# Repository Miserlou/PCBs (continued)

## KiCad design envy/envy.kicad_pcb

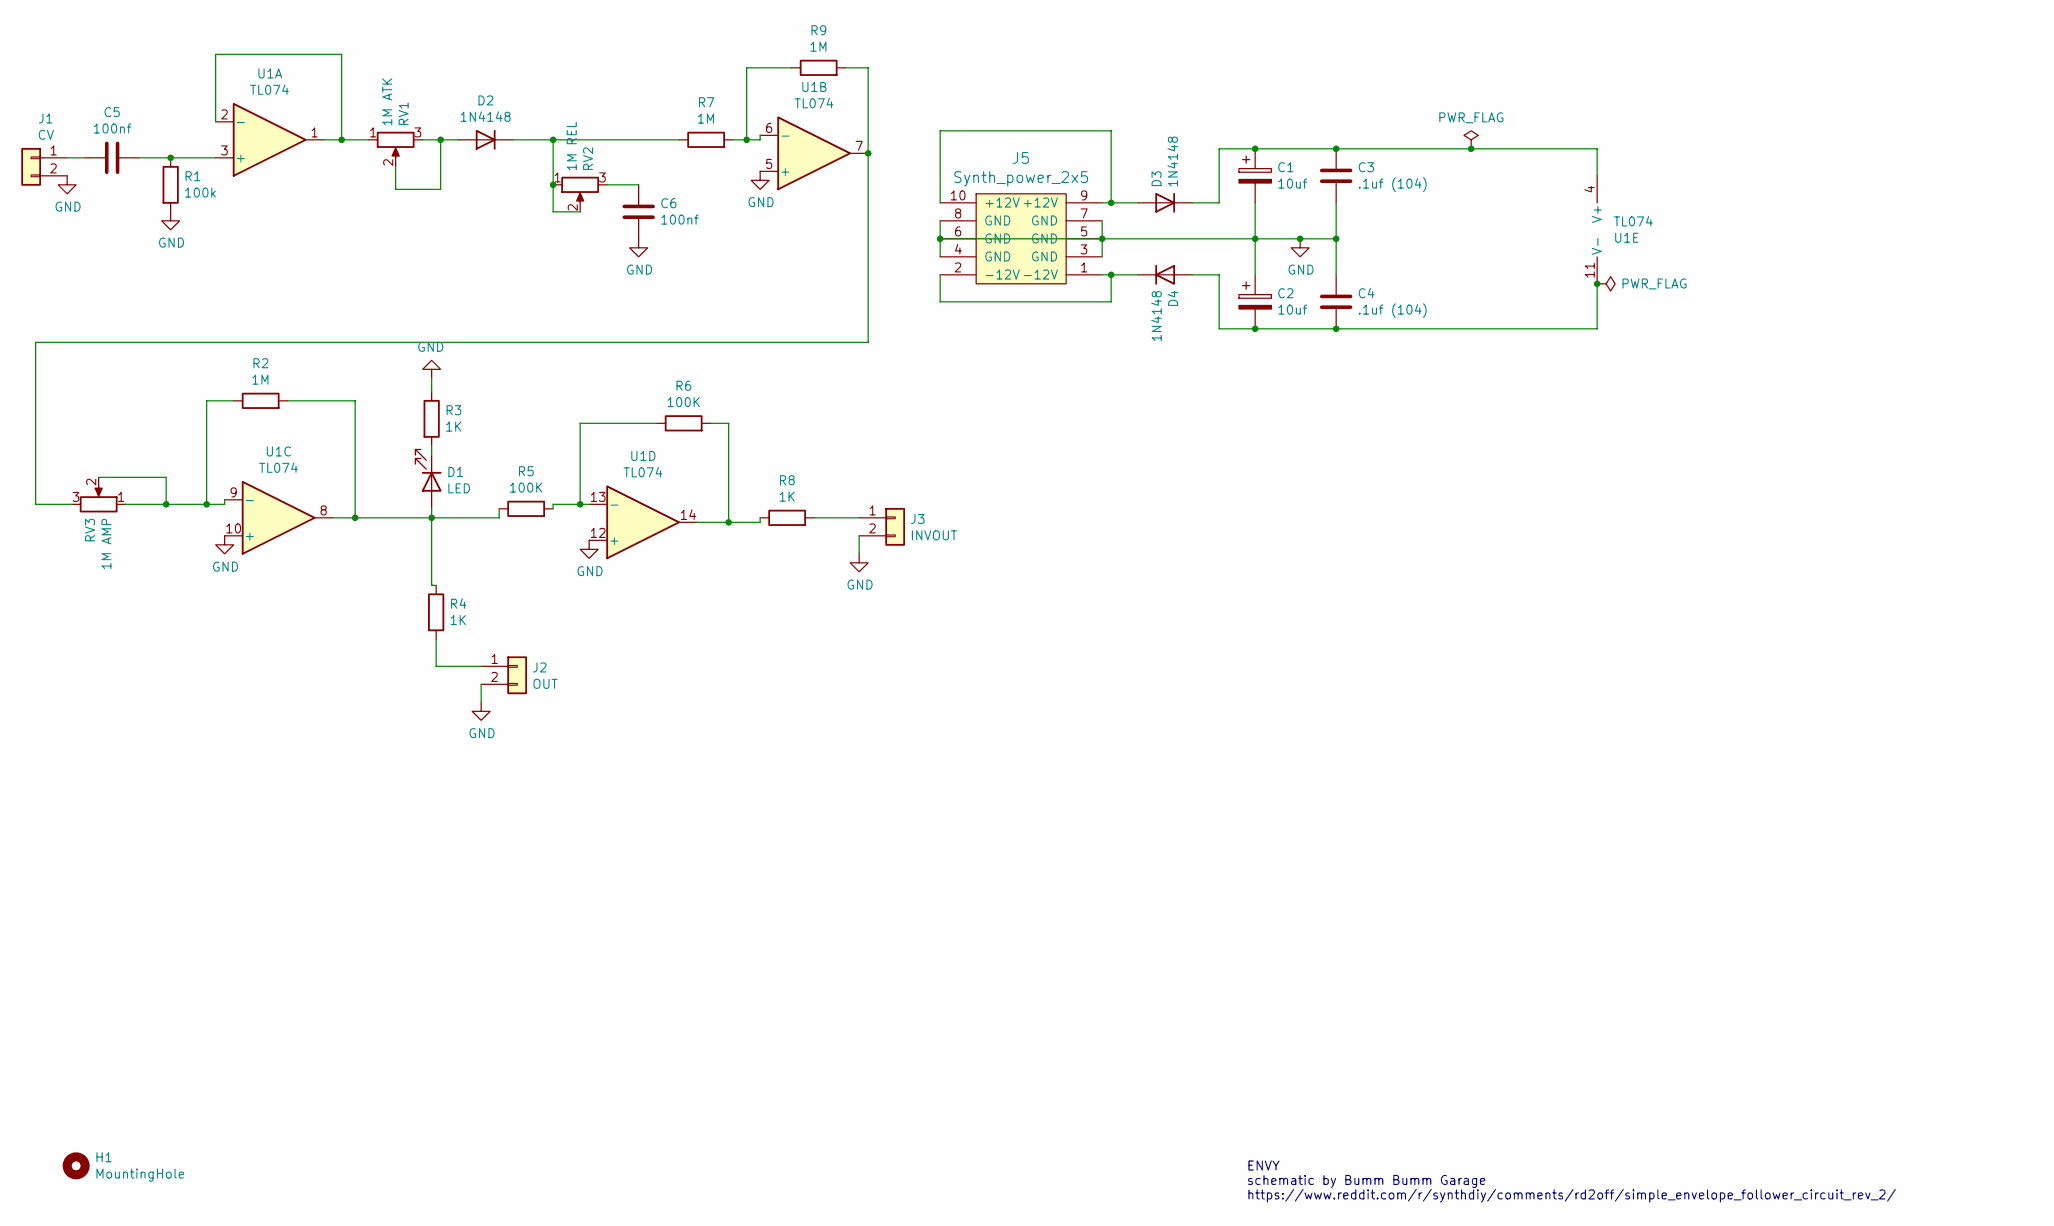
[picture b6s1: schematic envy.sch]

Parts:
C1, C2: 10uf; CP_Radial_D5.0mm_P2.00mm
C3, C4: .1uf (104); C_Disc_D3.0mm_W1.6mm_P2.50mm
C5, C6: 100nf; C_Disc_D3.0mm_W1.6mm_P2.50mm
D1: LED; LED_D5.0mm
D2, D3, D4: 1N4148; D_DO-35_SOD27_P7.62mm_Horizontal
H1: MountingHole; MountingHole_3.2mm_M3
J1: CV; Molex_KK-254_AE-6410-02A_1x02_P2.54mm_Vertical
J2: OUT; Molex_KK-254_AE-6410-02A_1x02_P2.54mm_Vertical
J3: INVOUT; Molex_KK-254_AE-6410-02A_1x02_P2.54mm_Vertical
J5: Synth_power_2x5; Power_Header
R1: 100k; R_Axial_DIN0207_L6.3mm_D2.5mm_P7.62mm_Horizontal
R2, R7, R9: 1M; R_Axial_DIN0207_L6.3mm_D2.5mm_P7.62mm_Horizontal
R3, R4, R8: 1K; R_Axial_DIN0207_L6.3mm_D2.5mm_P7.62mm_Horizontal
R5, R6: 100K; R_Axial_DIN0207_L6.3mm_D2.5mm_P7.62mm_Horizontal
RV1: 1M ATK; Potentiometer_Alpha_RD901F-40-00D_Single_Vertical_CircularH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
RV2: 1M REL; Potentiometer_Alpha_RD901F-40-00D_Single_Vertical_CircularH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
RV3: 1M AMP; Potentiometer_Alpha_RD901F-40-00D_Single_Vertical_CircularH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
U1: TL074; DIP-14_W7.62mm_Socket_LongPads

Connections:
GND: C1.2, C2.1, C3.2, C4.1, C6.2, J1.2, J2.2, J3.2, J5.3 (GND), J5.4 (GND), J5.5 (GND), J5.6 (GND), J5.7 (GND), J5.8 (GND), R1.2, R3.1, U1.5 (+), U1.10 (+), U1.12 (+); also elsewhere on the board
unnamed: C1.1, C3.1, D3.1 (K), U1.4 (V+)
unnamed: C2.2, C4.2, D4.2 (A), U1.11 (V-)
unnamed: C5.1, R1.1, U1.3 (+)
unnamed 4: C5.2, J1.1; also elsewhere on the board
unnamed: C6.1, RV2.3
unnamed: D1.1 (K), R3.2
unnamed: D1.2 (A), R2.2, R4.1, R5.1, U1.8
unnamed: D2.1 (K), R7.1, RV2.1, RV2.2
unnamed: D2.2 (A), RV1.2, RV1.3
unnamed: D3.2 (A), J5.9 (+12V), J5.10 (+12V)
unnamed: D4.1 (K), J5.1 (-12V), J5.2 (-12V)
unnamed: J2.1, R4.2
unnamed 13: J3.1, R8.2; also elsewhere on the board
unnamed: R2.1, RV3.1, RV3.2, U1.9 (-)
unnamed: R5.2, R6.1, U1.13 (-)
unnamed: R6.2, R8.1, U1.14
unnamed: R7.2, R9.1, U1.6 (-)
unnamed: R9.2, RV3.3, U1.7
unnamed: RV1.1, U1.1, U1.2 (-)

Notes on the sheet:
ENVY schematic by Bumm Bumm Garage https://www.reddit.com/r/synthdiy/comments/rd2off/simple_envelope_follower_circuit_rev_2/

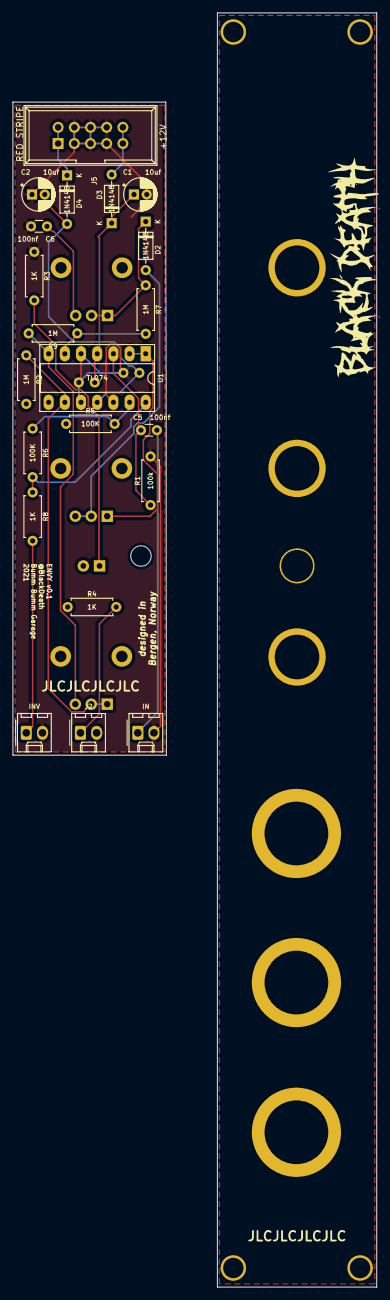
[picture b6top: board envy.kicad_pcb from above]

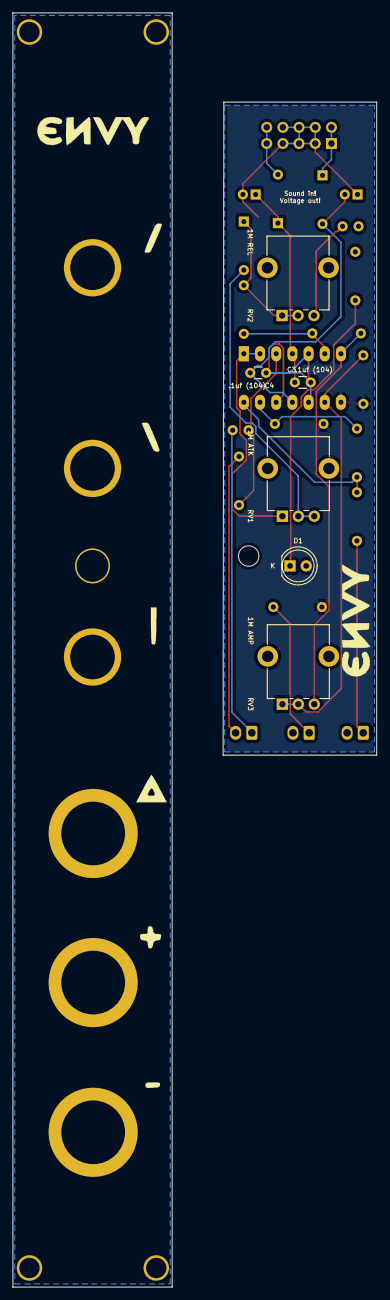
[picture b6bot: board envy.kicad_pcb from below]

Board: 2 copper layers, 57.1 x 200.0 mm, 28 parts (6 on the bottom side), 20 nets.

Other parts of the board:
IN: CV; Molex_KK-254_AE-6410-02A_1x02_P2.54mm_Vertical
INV: INVOUT; Molex_KK-254_AE-6410-02A_1x02_P2.54mm_Vertical

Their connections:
GND: IN.2, INV.2; also elsewhere on the board
unnamed 4: IN.1; also elsewhere on the board
unnamed 13: INV.1; also elsewhere on the board

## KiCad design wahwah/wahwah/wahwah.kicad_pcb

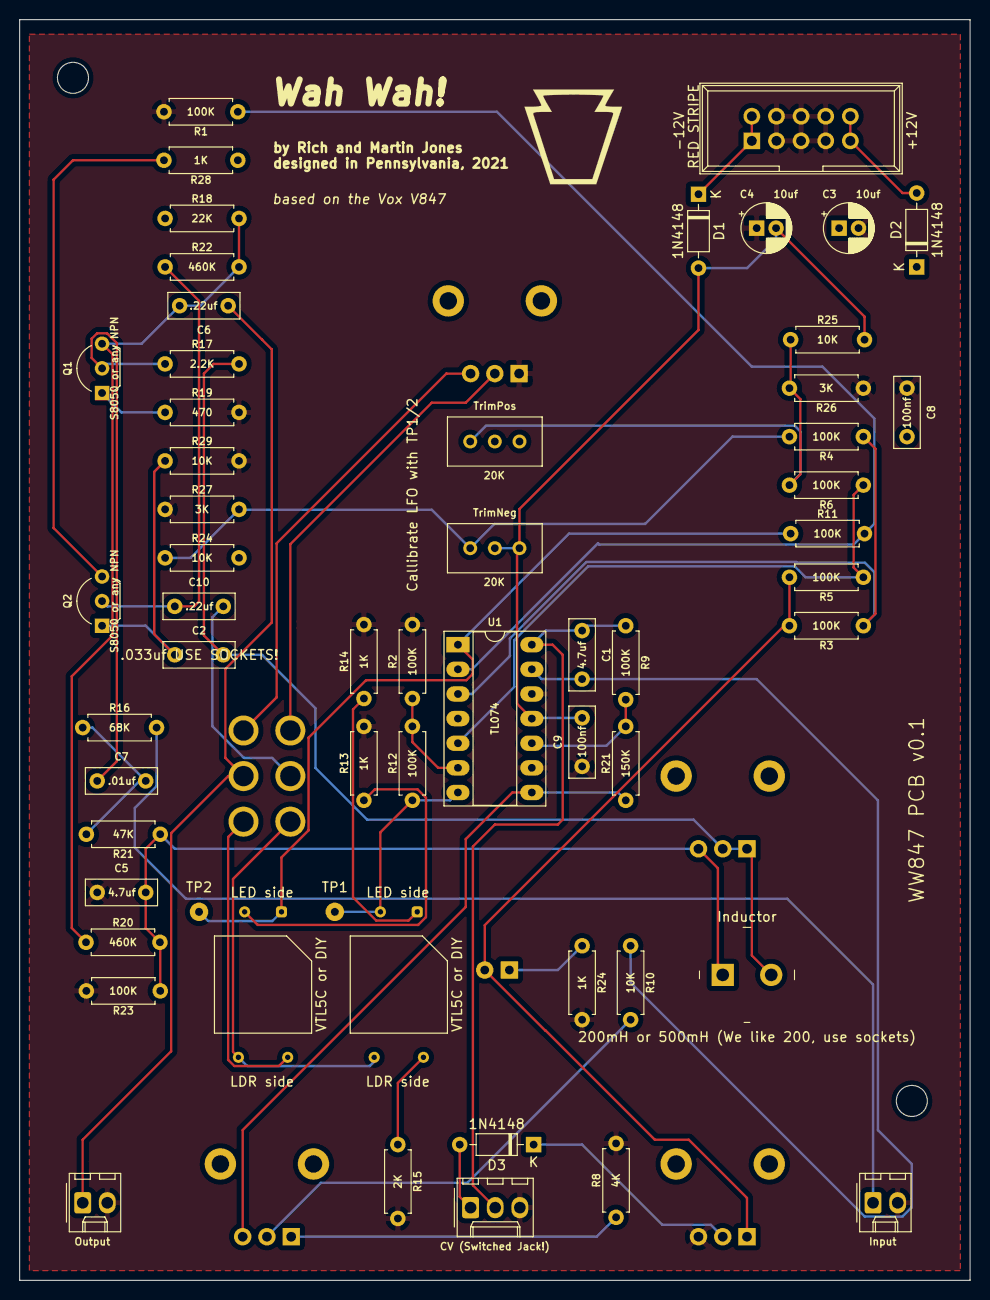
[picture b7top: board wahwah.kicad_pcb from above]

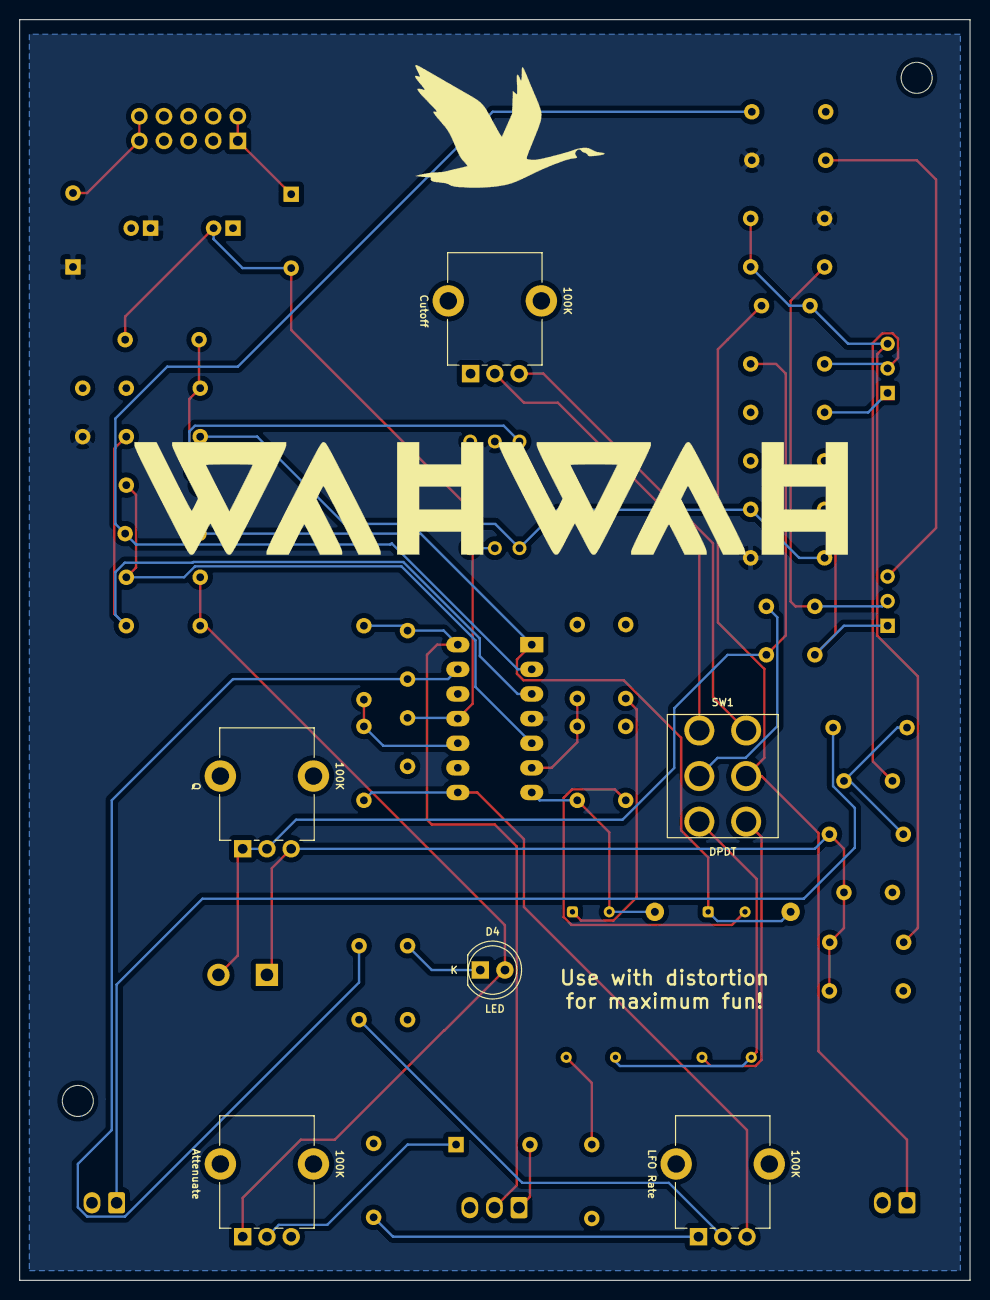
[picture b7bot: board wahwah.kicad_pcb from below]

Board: 2 copper layers, 98.0 x 130.0 mm, 65 parts (6 on the bottom side), 42 nets.

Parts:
Attenuate: 100K; Potentiometer_Alpha_RD901F-40-00D_Single_Vertical_CircularH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
C1, C5: 4.7uf; C_Rect_L7.2mm_W2.5mm_P5.00mm_FKS2_FKP2_MKS2_MKP2
C2: .033uf USE SOCKETS!; C_Rect_L7.2mm_W2.5mm_P5.00mm_FKS2_FKP2_MKS2_MKP2
C3, C4: 10uf; CP_Radial_D5.0mm_P2.00mm
C6, C10: .22uf; C_Rect_L7.2mm_W2.5mm_P5.00mm_FKS2_FKP2_MKS2_MKP2
C7: .01uf; C_Rect_L7.2mm_W2.5mm_P5.00mm_FKS2_FKP2_MKS2_MKP2
C8, C9: 100nf; C_Rect_L7.2mm_W2.5mm_P5.00mm_FKS2_FKP2_MKS2_MKP2
Cutoff: 100K; Potentiometer_Alpha_RD901F-40-00D_Single_Vertical_CircularH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
D1, D2, D3: 1N4148; D_DO-35_SOD27_P7.62mm_Horizontal
D4: LED; LED_D5.0mm
H1, H2: MountingHole; MountingHole_3.2mm_M3
Inductor: 200mH or 500mH (We like 200, use sockets); Inductor_13R106C
J1: Input; Molex_KK-254_AE-6410-02A_1x02_P2.54mm_Vertical
J2: Synth_power_2x5; Power_Header
J3: Output; Molex_KK-254_AE-6410-02A_1x02_P2.54mm_Vertical
J4: CV_switched_jack; Molex_KK-254_AE-6410-03A_1x03_P2.54mm_Vertical
LFO Rate: 100K; Potentiometer_Alpha_RD901F-40-00D_Single_Vertical_CircularH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
Q: 100K; Potentiometer_Alpha_RD901F-40-00D_Single_Vertical_CircularH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
Q1, Q2: S8050; TO-92_Inline_Wide
R1, R2, R3, R4, R5, R6, R9, R11, R12, R23: 100K; R_Axial_DIN0207_L6.3mm_D2.5mm_P7.62mm_Horizontal
R8: 4K; R_Axial_DIN0207_L6.3mm_D2.5mm_P7.62mm_Horizontal
R10, R24, R25, R29: 10K; R_Axial_DIN0207_L6.3mm_D2.5mm_P7.62mm_Horizontal
R13, R14, R24#2, R28: 1K; R_Axial_DIN0207_L6.3mm_D2.5mm_P7.62mm_Horizontal
R15: 2K; R_Axial_DIN0207_L6.3mm_D2.5mm_P7.62mm_Horizontal
R16: 68K; R_Axial_DIN0207_L6.3mm_D2.5mm_P7.62mm_Horizontal
R17: 2.2K; R_Axial_DIN0207_L6.3mm_D2.5mm_P7.62mm_Horizontal
R18: 22K; R_Axial_DIN0207_L6.3mm_D2.5mm_P7.62mm_Horizontal
R19: 470; R_Axial_DIN0207_L6.3mm_D2.5mm_P7.62mm_Horizontal
R20, R22: 460K; R_Axial_DIN0207_L6.3mm_D2.5mm_P7.62mm_Horizontal
R21: 150K; R_Axial_DIN0207_L6.3mm_D2.5mm_P7.62mm_Horizontal
R21#2: 47K; R_Axial_DIN0207_L6.3mm_D2.5mm_P7.62mm_Horizontal
R26, R27: 3K; R_Axial_DIN0207_L6.3mm_D2.5mm_P7.62mm_Horizontal
SW1: SW_DPDT_x2; DPDT-toggle-switch-1M-seriesx
TP1, TP2: TestPoint; Perf_Board_Hole
TrimNeg: 20K; Potentiometer_Bourns_3296W_Vertical
TrimPos: 20K; Potentiometer_Bourns_3296W_Vertical
U1: TL074; DIP-14_W7.62mm_Socket_LongPads
VTL5C or DIY, VTL5C or DIY#2: VTL5C; PerkinElmer_VTL5C

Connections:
+12V: C3.1, C8.2, D2.1, R18.1, R24.2, R28.1, TrimPos.1, TrimPos.2, U1.4
A: R6.2, R25.1, R26.2, TrimPos.3
B: R4.2, R24.1, R27.2, TrimNeg.3
D: SW1.1, VTL5C or DIY.3
E: SW1.4, VTL5C or DIY.4, VTL5C or DIY#2.4
F: Cutoff.3, SW1.3
G: Cutoff.2, SW1.6
GND: Attenuate.3, C3.2, C4.1, C5.1, C8.1, C9.1, Cutoff.1, J1.2, J2.3, J2.4, J2.5, J2.6, J2.7, J2.8, J3.2, J4.3, R1.2, R2.2, R8.2, R13.2, R14.2, R15.2, R19.2, R23.2, R24#2.2, R26.1, R27.1, R29.2, U1.9, U1.12
I: C6.1, J3.1, SW1.2
J: C10.2, SW1.5
unnamed: Attenuate.2, D3.1
unnamed: C1.1, J4.2, R9.1, U1.14
unnamed: C1.2, R10.1, U1.13
unnamed: C2.1, Q2.1, R29.1
unnamed: C2.2, Inductor.2, Q.1, Q.2, R17.2
unnamed: C4.2, C9.2, D1.2, R25.2, TrimNeg.1, TrimNeg.2, U1.11
unnamed: C5.2, Inductor.1, Q.3, R20.2, R21#2.1, R23.1
unnamed: C6.2, Q1.3, R18.2, R20.1, R22.2
unnamed: C7.1, Q1.2, R17.1
unnamed: C7.2, R16.1, R21#2.2
unnamed: C10.1, Q2.2, R22.1
unnamed: D1.1, J2.1, J2.2
unnamed: D2.2, J2.9, J2.10
unnamed: D3.2, J4.1
unnamed: D4.1, R24#2.1
unnamed: J1.1, R16.2
unnamed: LFO Rate.1, R8.1
unnamed: LFO Rate.2, R10.2
unnamed: LFO Rate.3, R21.1, U1.8
unnamed: Q1.1, R19.1
unnamed: Q2.3, R28.2
unnamed: R1.1, R11.2, U1.2
unnamed: R3.1, R4.1, U1.3
unnamed: R5.1, R6.1, U1.5
unnamed: R11.1, TP2.1, U1.1, VTL5C or DIY.1
unnamed: R12.1, TP1.1, U1.7, VTL5C or DIY#2.2
unnamed: R2.1, R12.2, U1.6
unnamed: R13.1, VTL5C or DIY.2
unnamed: R14.1, VTL5C or DIY#2.1
unnamed: R15.1, VTL5C or DIY#2.3
unnamed: R9.2, R21.2, U1.10
X: Attenuate.1, D4.2, R3.2, R5.2

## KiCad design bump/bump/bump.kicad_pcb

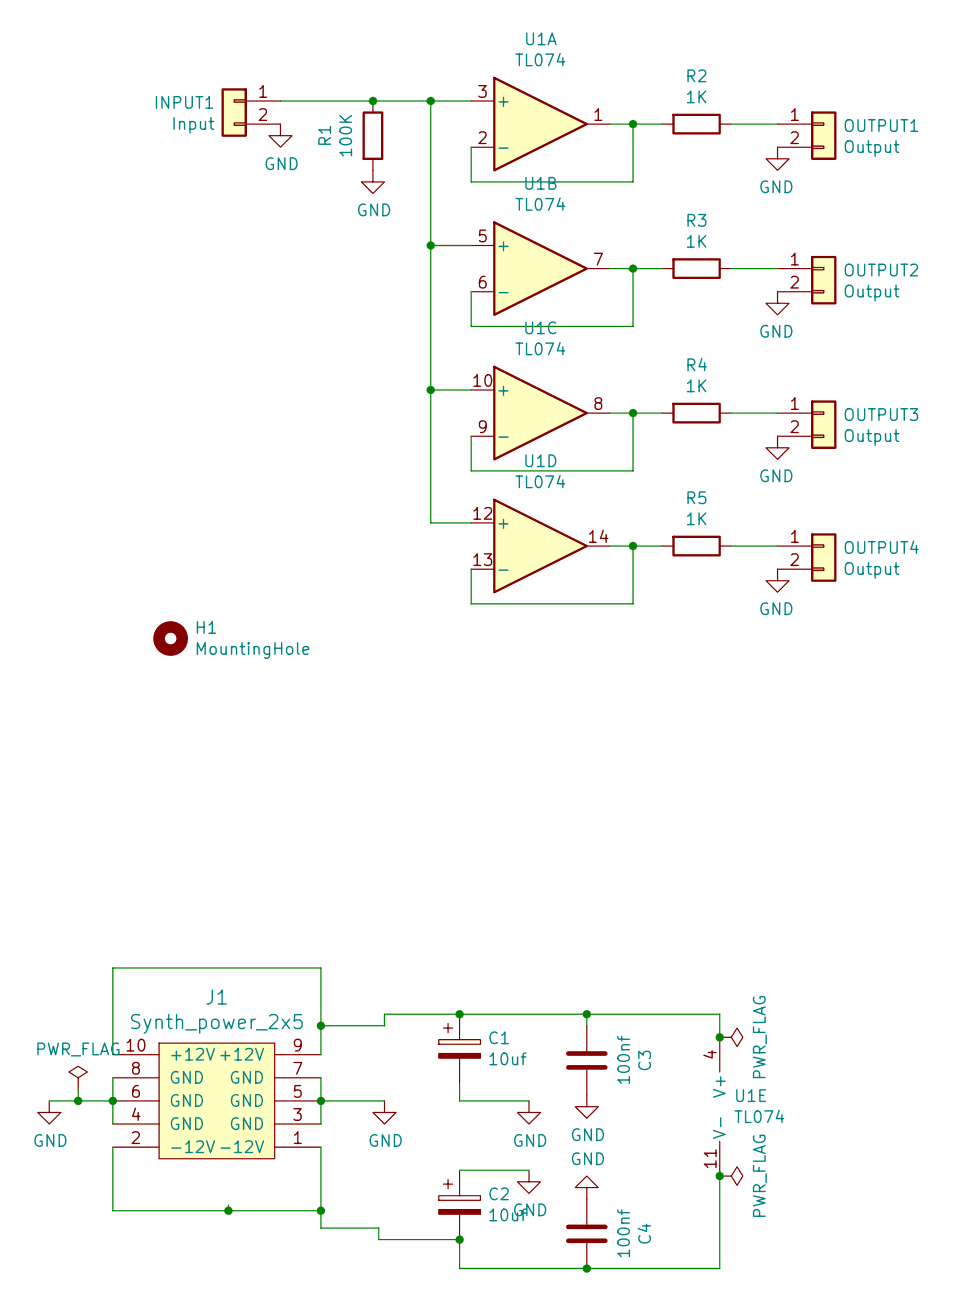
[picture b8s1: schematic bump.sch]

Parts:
C1, C2: 10uf; CP_Radial_D5.0mm_P2.00mm
C3, C4: 100nf; C_Disc_D3.0mm_W1.6mm_P2.50mm
H1: MountingHole; MountingHole_3.2mm_M3
INPUT1: Input; Molex_KK-254_AE-6410-02A_1x02_P2.54mm_Vertical
J1: Synth_power_2x5; Power_Header
OUTPUT1, OUTPUT2, OUTPUT3, OUTPUT4: Output; Molex_KK-254_AE-6410-02A_1x02_P2.54mm_Vertical
R1: 100K; R_Axial_DIN0207_L6.3mm_D2.5mm_P7.62mm_Horizontal
R2, R3, R4, R5: 1K; R_Axial_DIN0207_L6.3mm_D2.5mm_P7.62mm_Horizontal
U1: TL074; DIP-14_W7.62mm_Socket_LongPads

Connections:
GND: C1.2, C2.1, C3.1, C4.2, INPUT1.2, J1.3 (GND), J1.4 (GND), J1.5 (GND), J1.6 (GND), J1.7 (GND), J1.8 (GND), OUTPUT1.2, OUTPUT2.2, OUTPUT3.2, OUTPUT4.2, R1.2
unnamed: C1.1, C3.2, J1.9 (+12V), J1.10 (+12V), U1.4 (V+)
unnamed: C2.2, C4.1, J1.1 (-12V), J1.2 (-12V), U1.11 (V-)
unnamed: INPUT1.1, R1.1, U1.3 (+), U1.5 (+), U1.10 (+), U1.12 (+)
unnamed: OUTPUT1.1, R2.1
unnamed: OUTPUT2.1, R3.1
unnamed: OUTPUT3.1, R4.1
unnamed: OUTPUT4.1, R5.1
unnamed: R2.2, U1.1, U1.2 (-)
unnamed: R3.2, U1.6 (-), U1.7
unnamed: R4.2, U1.8, U1.9 (-)
unnamed: R5.2, U1.13 (-), U1.14

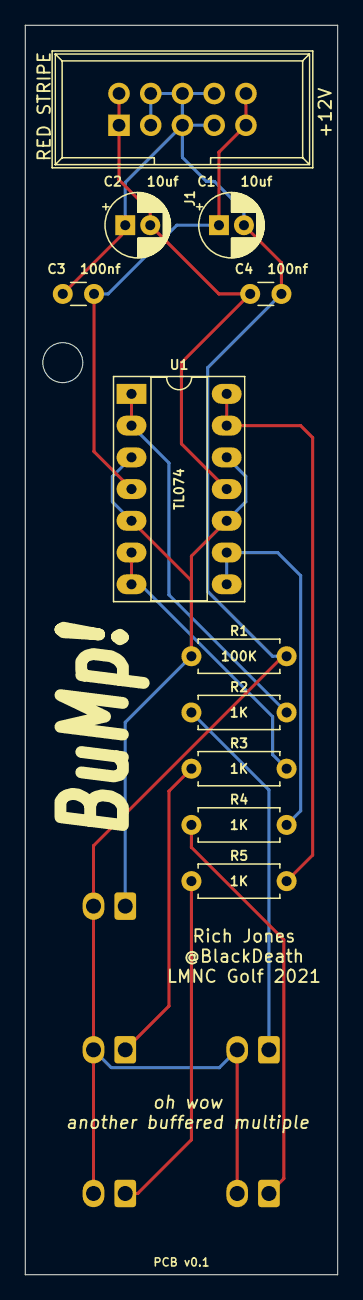
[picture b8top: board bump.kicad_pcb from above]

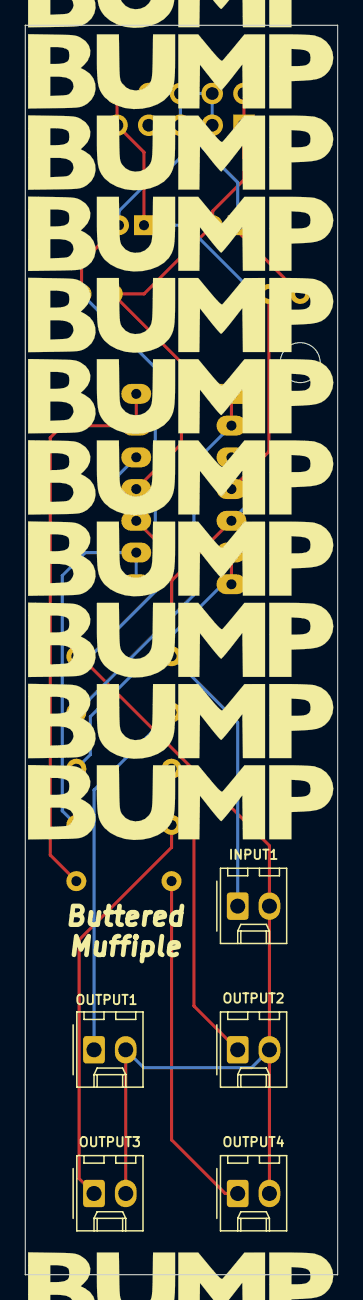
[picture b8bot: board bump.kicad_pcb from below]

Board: 2 copper layers, 25.0 x 100.0 mm, 17 parts (5 on the bottom side), 12 nets.

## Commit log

2021-07-06 start
2021-09-08 buncha
2021-10-08 eyeyey
2021-11-22 kross
2021-11-22 more
2021-12-05 sub work
2021-12-09 routed
2021-12-09 nice
2021-12-11 envy
2021-12-12 more envy
2021-12-13 gerbers
2021-12-13 blah
2023-07-25 add springy
2023-08-06 finalize xorcist spring niga
2024-12-09 warning readme
